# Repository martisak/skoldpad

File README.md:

<p align="center">
  <picture>
    <source media="(prefers-color-scheme: dark)" srcset="./images/header-white.svg">
    <source media="(prefers-color-scheme: light)" srcset="./images/header-black.svg">
    
  </picture>
</p>

A split, columnar-staggered keyboard built around a
[nice!nano](https://nicekeyboards.com/nice-nano/) MCU with a rotary encoder, laid out with
[ergogen](https://github.com/ergogen/ergogen) and routed in KiCad. It's based on/inspired by
[josukey](https://github.com/Narkoleptika/josukey) (MIT licensed), an ergogen-based Corne clone.

Firmware ([ZMK](https://zmk.dev/), with a custom keymap tuned for Swedish input and coding
symbols) lives in its own repo: **[martisak/zmk-config](https://github.com/martisak/zmk-config)**.

## Renders

## Prerequisites

* Node
* KiCad (to open/edit the PCB)

## Getting Started

```bash
git clone https://github.com/martisak/skoldpad.git
cd skoldpad
npm i
```

## Ergogen

The layout lives in `ergogen/config.yaml`.

### Build

Runs Ergogen and builds all of the output files (outlines, case, PCB skeleton) into `ergogen/output`.

```bash
npm run ergogen:build
```

### Watch

Watches `config.yaml` and the `footprints` directory and re-runs the build on changes.

```bash
npm run ergogen:watch
```

## KiCad

The hand-routed PCB lives at [`ergogen/kicad/skoldpad.kicad_pcb`](./ergogen/kicad/skoldpad.kicad_pcb)
(along with the schematic, 3D step model, and the custom `Skoldpad.pretty` footprint library it
depends on) — open `ergogen/kicad/skoldpad.kicad_pro` in KiCad.

<p align="center">
  <picture>
    <source media="(prefers-color-scheme: dark)" srcset="./images/schematic-dark.svg">
    <source media="(prefers-color-scheme: light)" srcset="./images/schematic-light.svg">
    
  </picture>
</p>

Regenerate these from the routed board with `make schematics` (requires `kicad-cli` and Python 3
on `PATH`); see the [`Makefile`](./Makefile).

## Firmware

Firmware and keymap are maintained separately at
[martisak/zmk-config](https://github.com/martisak/zmk-config):

```bash
git clone git@github.com:martisak/zmk-config.git
```

It's a [nice!nano](https://nicekeyboards.com/nice-nano/) ZMK build with its own keymap (not
based on Miryoku), tuned for the macOS Swedish layout — base layer plus NUM, FUNC, and
directional layers. Builds run in GitHub Actions on every push; grab the `.uf2` artifacts from
the latest successful run.

The PCB footprints support a [nice!view](https://nicekeyboards.com/nice-view) display — this
should work but hasn't been tested yet.

## Case

The case is designed in [Shapr3D](https://app.shapr3d.com/p/ba8f4a1e-6f99-4bed-8f1e-6df41bfcee0b)
(viewable in 3D at that link) and 3D printed. STL files for both halves (top and bottom shells)
are in [`case/`](./case):

* [`case/left.stl`](./case/left.stl) / [`case/left_top.stl`](./case/left_top.stl)
* [`case/right.stl`](./case/right.stl) / [`case/right_top.stl`](./case/right_top.stl)

## Bill of Materials

Quantities below are **per half**; this design is one hand's PCB, fabricated twice (one
normal, one mirrored) for a complete pair — double everything for a full two-hand build.

**This PCB is Choc v1 (PG1350) only.** The switch footprint's center hole and stabilizer-leg
positions don't match Choc v2 or MX, so neither is a drop-in substitution — see Future Work.

| Part | Qty/half | Notes |
|---|---:|---|
| [nice!nano](https://nicekeyboards.com/nice-nano/) | 1 | MCU, one per half (each half is an independent BLE unit) |
| [nice!view](https://nicekeyboards.com/nice-view) | 1 | Display — **untested**, see Known Issues; optional |
| Panasonic EVQWGD001 rotary encoder | 1 | ⚠️ Discontinued by Panasonic — check old-stock listings (e.g. [Jotrin](https://www.jotrin.com/product/parts/EVQWGD001)) or plan to substitute a pin-compatible EVQW-series encoder |
| Kailh Choc v1 switch | 23 | See Future Work — v2 is the recommended switch going forward |
| Kailh PG1350 hotswap socket | 23 | Choc v1 hotswap socket, e.g. [Chosfox](https://chosfox.com/products/kailh-choc-switch-1350-hot-swap-sockets) |
| SOD-123W diode (e.g. 1N4148W) | 23 | Standard keyboard-matrix switching diode |
| JST PH 2-pin connector (S2B-PH-K, 2.0mm) | 1 | Battery connector |
| LiPo battery (JST PH 2-pin) | 1 | Capacity not specified by the design — pick to fit the case |
| Kailh PCM12 SPDT slide switch | 1 | Power on/off |
| Würth WS-TASV SMT tactile switch ([434121025816](https://www.digikey.com/en/products/detail/w%C3%BCrth-elektronik/434121025816/5209078)) | 1 | Reset button |
| M2 screws + threaded inserts/standoffs | 11 sets | One per mounting point in `config.yaml` (`screw_*` positions) |
| 1u keycap (Choc profile) | 21 | |
| 1.5u keycap (Choc profile) | 2 | Thumb keys — see Known Issues re: rotation |

Not in the PCB itself but needed to finish a build: the 3D-printed case (see Case section
above) and a filament of your choice.

## Known Issues

* The two thumb keys should be rotated to accept a 1.5u keycap, as shown in the renders.
* nice!view support is untested — should work per the footprint, but not confirmed on hardware.
* The case's screw posts are thin and prone to cracking when installing the threaded inserts
  (see Bill of Materials — M2 screws + threaded inserts/standoffs); consider thickening the
  posts in the Shapr3D model or heat-setting inserts more carefully.

## Future Work

* Move to Choc v2 switches — currently on v1, which has a smaller center post than v2.
* Test compatibility with full-size MX switches.
* Test nice!view once one arrives (currently on order).
* Update the BOM's rotary encoder — the specified Panasonic EVQWGD001 is discontinued;
  find and validate a pin-compatible replacement.
* Consider per-key LEDs instead of underglow — underglow would need a transparent case,
  which the current 3D-printed design isn't.

## License

Code (footprint generator scripts, build tooling) is [MIT](./LICENSE). The
hardware design (PCB, schematic, case, and ergogen layout) is
[CC BY-NC-SA 4.0](./LICENSE-HARDWARE), matching the license of the nice!nano
and nice!view footprints it incorporates (see Thanks below).

## Thanks

* <a href="https://github.com/ergogen/ergogen" target="_blank">Ergogen</a>
* <a href="https://discord.gg/nbKcAZB" target="_blank">Absolem Club Discord</a>
* <a href="https://github.com/infused-kim/kb_ergogen_fp" target="_blank">@infused-kim</a>
  for the original nice!nano and nice!view footprints, and
  <a href="https://github.com/ceoloide/ergogen-footprints" target="_blank">@ceoloide</a>
  for maintaining and upgrading them to KiCad 8 (both CC BY-NC-SA 4.0)
* <a href="https://github.com/tsteffek/Ergogen-V4-Migration-Guide" target="_blank">V4 Migration Guide</a>
* <a href="https://gitlab.com/Audijo/keyboard" target="_blank">Claw</a>
* <a href="https://github.com/MrCarney/mrkeyboard" target="_blank">MrKeyboard</a>
* <a href="https://github.com/foostan/crkbd" target="_blank">Corne keyboard</a>
* <a href="https://www.youtube.com/watch?v=dg2TT1OJlQs" target="_blank">Ben Vallack</a>
* <a href="https://github.com/zmkfirmware/zmk" target="_blank">ZMK</a>
* <a href="https://github.com/Narkoleptika/josukey" target="_blank">josukey</a> — the base this board started from
* <a href="https://sv.wikipedia.org/wiki/V%C3%A4sterg%C3%B6tlands_landskapsvapen" target="_blank">Västergötlands landskapsvapen</a> — inspiration for the logo
* <a href="https://fonts.google.com/specimen/Chakra+Petch" target="_blank">Chakra Petch</a> — typeface used for PCB text and case engraving

## AI Disclosure

Claude (Anthropic) assisted with README and documentation polish — drafting and formatting
text (including the BOM table and general presentation of this repo) from the author's own
notes and decisions. The design, PCB, firmware, fabrication work, and content substance
(including Known Issues and Future Work) are the author's own.

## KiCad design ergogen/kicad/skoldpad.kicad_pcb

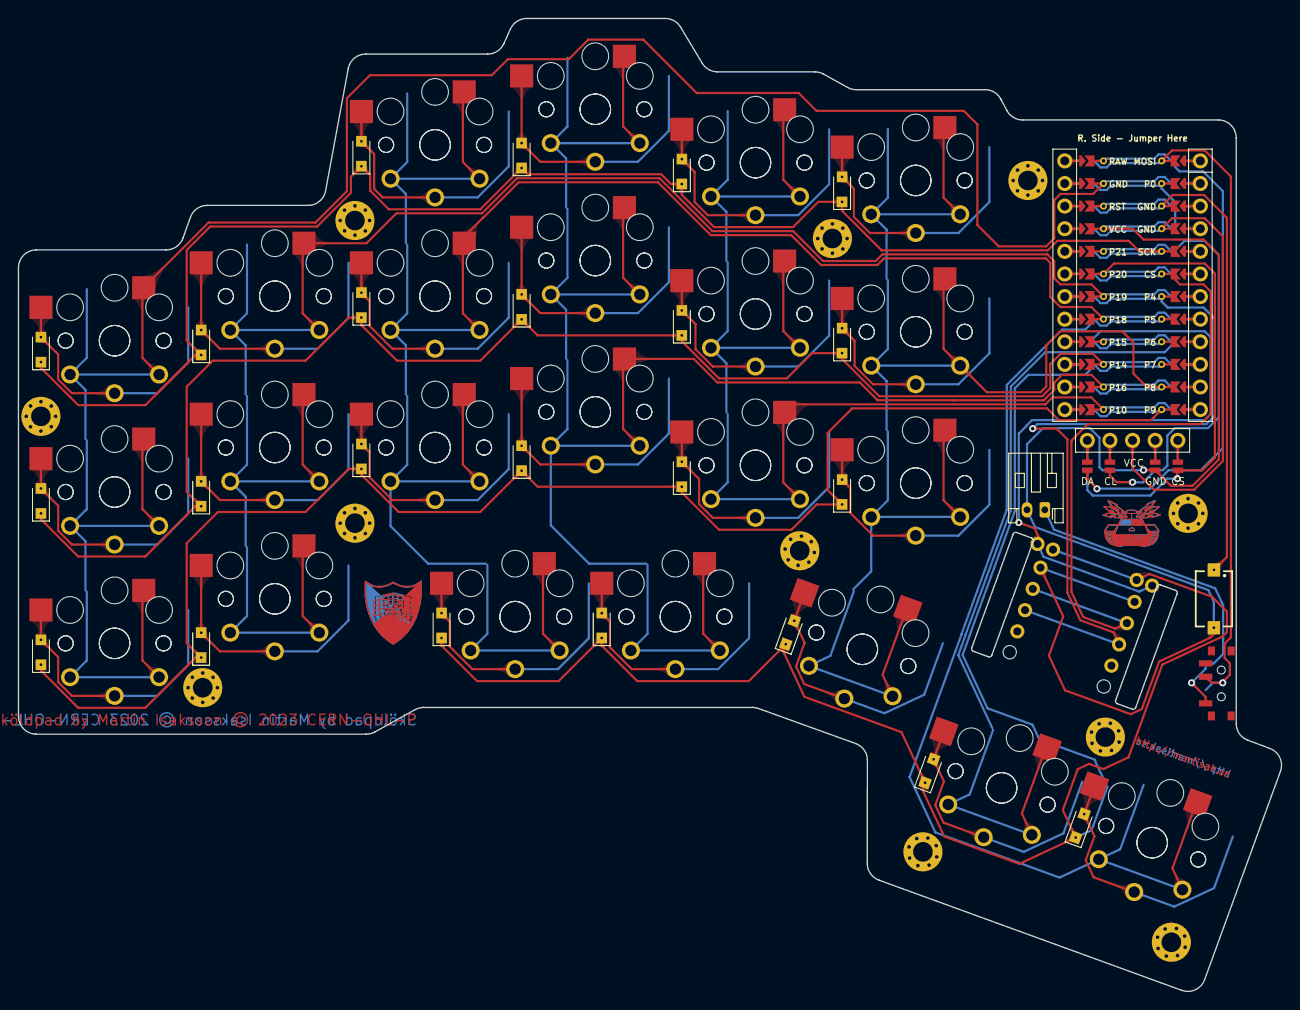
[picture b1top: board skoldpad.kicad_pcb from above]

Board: 2 copper layers, 141.9 x 109.3 mm, 85 parts (0 on the bottom side), 47 nets.

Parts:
D1, D2, D3, D4, D5, D6, D7, D8, D9, D10, D11, D12, D13, D14, D15, D16, D17, D18, D19, D20, D21, D22, D23: Nexperia_CFP3_SOD-123W
DISP1: nice!view
H1, H2, H3, H4, H5, H6, H7, H8, H9, H10, H11: MountingHole_2.2mm_M2_Pad_Via
MCU1: nice_nano
S1, S2, S3, S4, S5, S6, S7, S8, S9, S10, S11, S12, S13, S14, S15, S16, S17, S18, S19, S20, S21, S22, S23, S24, S25, S26, S27, S28, S29, S30, S31, S32, S33, S34, S35, S36, S37, S38, S39, S40, S41, S42, S43, S44, S45, S46: PG1350
S48: 434121025816
T1: SW_SPDT_PCM12
_1: JST_PH_S2B-PH-K_1x02_P2.00mm_Horizontal

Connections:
CS: DISP1.13, DISP1.23, MCU1.119
DISP1_1: DISP1.1, DISP1.14, DISP1.27
DISP1_2: DISP1.2, DISP1.15, DISP1.26
DISP1_4: DISP1.4, DISP1.16, DISP1.25
DISP1_5: DISP1.5, DISP1.17, DISP1.24
GND: DISP1.12, DISP1.22, MCU1.2, MCU1.121, MCU1.122, S48.2, _1.2
MOSI: DISP1.10, DISP1.20, MCU1.124
P0: MCU1.123, S1.1, S2.1, S3.1, S24.1, S25.1, S26.1
P4: MCU1.118, S4.1, S5.1, S6.1, S27.1, S28.1, S29.1
P5: MCU1.117, S7.1, S8.1, S9.1, S19.1, S30.1, S31.1, S32.1, S42.1
P6: MCU1.116, S22.1, S45.1
P7: D2.1, D5.1, D8.1, D11.1, D19.1, D22.1, MCU1.115
P8: MCU1.114, S10.1, S11.1, S12.1, S20.1, S33.1, S34.1, S35.1, S43.1
P9: MCU1.113, S13.1, S14.1, S15.1, S36.1, S37.1, S38.1
P10: D1.1, D4.1, D7.1, D10.1, D18.1, D21.1, MCU1.12
P14: D13.1, D14.1, D15.1, D16.1, D17.1, MCU1.10
P16: MCU1.11, S16.1, S17.1, S18.1, S21.1, S39.1, S40.1, S41.1, S44.1
P18: MCU1.8, S23.1, S46.1
P21: D3.1, D6.1, D9.1, D12.1, D20.1, D23.1, MCU1.5
RAW: MCU1.1, T1.2
RST: MCU1.3, S48.1
SCK: DISP1.11, DISP1.21, MCU1.120
VCC: DISP1.3, MCU1.4
control_farinner_home: D13.2, S19.2, S42.2
control_home_home: D15.2, S21.2, S44.2
control_inner_home: D14.2, S20.2, S43.2
main_index_bottom: D7.2, S13.2, S36.2
main_index_home: D8.2, S14.2, S37.2
main_index_top: D9.2, S15.2, S38.2
main_inner_bottom: D10.2, S16.2, S39.2
main_inner_home: D11.2, S17.2, S40.2
main_inner_top: D12.2, S18.2, S41.2
main_middle_bottom: D21.2, S10.2, S33.2
main_middle_home: D22.2, S11.2, S34.2
main_middle_top: D23.2, S12.2, S35.2
main_outer_bottom: D1.2, S1.2, S24.2
main_outer_home: D2.2, S2.2, S25.2
main_outer_top: D3.2, S3.2, S26.2
main_pinky_bottom: D18.2, S4.2, S27.2
main_pinky_home: D19.2, S5.2, S28.2
main_pinky_top: D20.2, S6.2, S29.2
main_ring_bottom: D4.2, S7.2, S30.2
main_ring_home: D5.2, S8.2, S31.2
main_ring_top: D6.2, S9.2, S32.2
pos: T1.1, _1.1
thumb_middle_home: D16.2, S22.2, S45.2
thumb_outer_home: D17.2, S23.2, S46.2

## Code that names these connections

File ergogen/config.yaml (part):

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        # Mounting screws             
        screw_bottom_left:
          anchor:
            ref.aggregate.parts: [main_outer_bottom, main_pinky_bottom]
            shift: [0.05kx,-0.44ky]
          columns.screw.key.tags: [screw]
        screw_top_left:
          anchor:
            ref.aggregate.parts: [main_pinky_top, main_ring_home]
            shift: [0kx,0.5ky]
          columns.screw.key.tags: [screw]
        screw_middle:
          anchor:
            ref.aggregate.parts: [main_ring_bottom, main_pinky_bottom]
            shift: [0, 0]
          columns.screw.key.tags: [screw]
        screw_mcu:
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                -   ref: main_outer_top
                    shift: [0.4kx, 0.6ky]
                
                -   ref: main_pinky_top
                    shift: [-0.5kx, 0.6ky]
                -   ref: main_pinky_top
                    shift: [0.3kx, 0.6ky]

                -   ref: main_ring_top
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            what: text
            where:
              ref:
                - main_pinky_bottom
              shift: [0.05kx, -0.8ky]
            adjust:
                rotate: 90
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            what: text
            where:
              ref:
                - main_pinky_bottom
              shift: [0.05kx, -0.8ky]
            adjust:
                rotate: 90
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

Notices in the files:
ergogen/kicad/skoldpad.kicad_pcb:
© 2023 CERN-OHL-P
parts and their libraries:
Sköldpad by Martin Isaksson © 2023 CERN-OHL-P
